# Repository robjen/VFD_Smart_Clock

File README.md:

# VFD_Smart_Clock

A Series of 'socket' designs and firmware running on ESP8266 for IoT smart clock

first draft of working firmware :
https://www.youtube.com/watch?v=jQWC35hEyko

Sockets are 1-4 digits in all sorts of size based on:
* 4 digits IV4/17 16 segment tube
* 1 digit 5x7 IV26 7 point tubes type 1 (fully independant dots) and type 3  (1-2-1-2-1 )
* 2 digits 2x 5x7 IV25 7 point tubes type 1 and type 3 (yes found these on the internet named them as above)
* LED lighting under/behind each tube with a WS2812 RGB 
* HV module on each board so they are fully independant and run from a single 5V supply
* 4 digital lines for easy control passed though each board SPI-clk SPI-data SPI-load BLANK LED-data

Any of the types of socket can be chained, but you might have to mess about with the firmware if you want mix-n-match different types

Firmware provides:
* clock display 
* NTP sync
* auto DST based on timezone
* hidden 'phrases'
* RSS news reader (BBC)
* Ability to add user messages
* Web interface for configuration
* a load of animated transitions and effects
* a few LED effects (more coming soon)

loads of new features coming soon

its a bit of a mess right now but in progress

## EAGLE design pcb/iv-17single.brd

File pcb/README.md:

# eagle cad files for 5 types of PCB

not the best naming convention but load them to see whats what

all of them have been sent off for manufacture at http://dirtypcbs.com and work

simple layout for easy hand soldering including everything in sockets

I switched convention on the IV25 and started calling them type 1 and type 3 to match the IV26 tubes the PCB mask layer reflects that even if the PCB schematic does not

# Tubes ....

well they are getting harder to find but ebay is your friend, also use the 'international' .com site as I find the UK site sometimes hides possible sellers that will still ship to here and quote prices in dollars

# Components 

the main IC ... you can use that maxim part but its pricey or a perfect substitute is the 'HV5812' again ebay is the place to find those

WS2812b again ebay cheap and easy to find in reels ready to solder, that and 1 capacitor are surface mount (on the IV4/17 board) easy enough with a steady hand

the DC-DC module was again an ebay thing (can you spot a trend here!)  there are loads of far east manufactures doing a module that should be about £1 including post per module.  you could use one module to power more than 1 PCB with a fly-lead thats up to you, keeping 1 module per PCB means you can mix and match anything you want. 

# BIG SOLDER TIP

The hardest part can be threading the tubes and getting them all nice and level.

Note the marker point on each PCB, sometimes this is the short (almost removed) pin, sometimes the longest pin, sometimes just a vague guide ... it will depend where you sourced your tubes from, check and check again before you solder as there is no going back. the PCB layout is as per data sheet but these tubes have an element of 'hand made' so not 100% perfect they should face forward give or take a tiny adjustment.

I found that for tubes with few wires it is easy enough to align them all by hand in one go and push whole tube down in one step.

For tubes with lots of wires (IV4/17) start by threading a few on one side then work round with tweezers loading each wire in turn until you can push the whole tube home.

DO NOT use the glass envelope of the tube to try and align the digits, they vary quite a lot internally so allow a gap above the PCB on the first one you solder and alight the 'dots' or digits by eye or with a rule to get them even. If you dont allow a gap on the first one you might find you cant push subsequent ones down low enough ... 

At this point in construction I tended to tape everything down to a spare board as I went so that all the tubes were well aligned and I can fip it up and solder

KEEP YOUR FIRST EXAMPLE at least the first one you are happy with, then you can use it as a guide of height of dot/digit from the PCB for subsequent builds  (I use a scrap early PCB design that had an error but the tubes are neat so its a good guide).

you can adjust tubes a little once soldered but there is a risk you will break the pins or short something if you try and squash the tubes down. you cant really do more than a tiny twist on the IV4/17 tubes

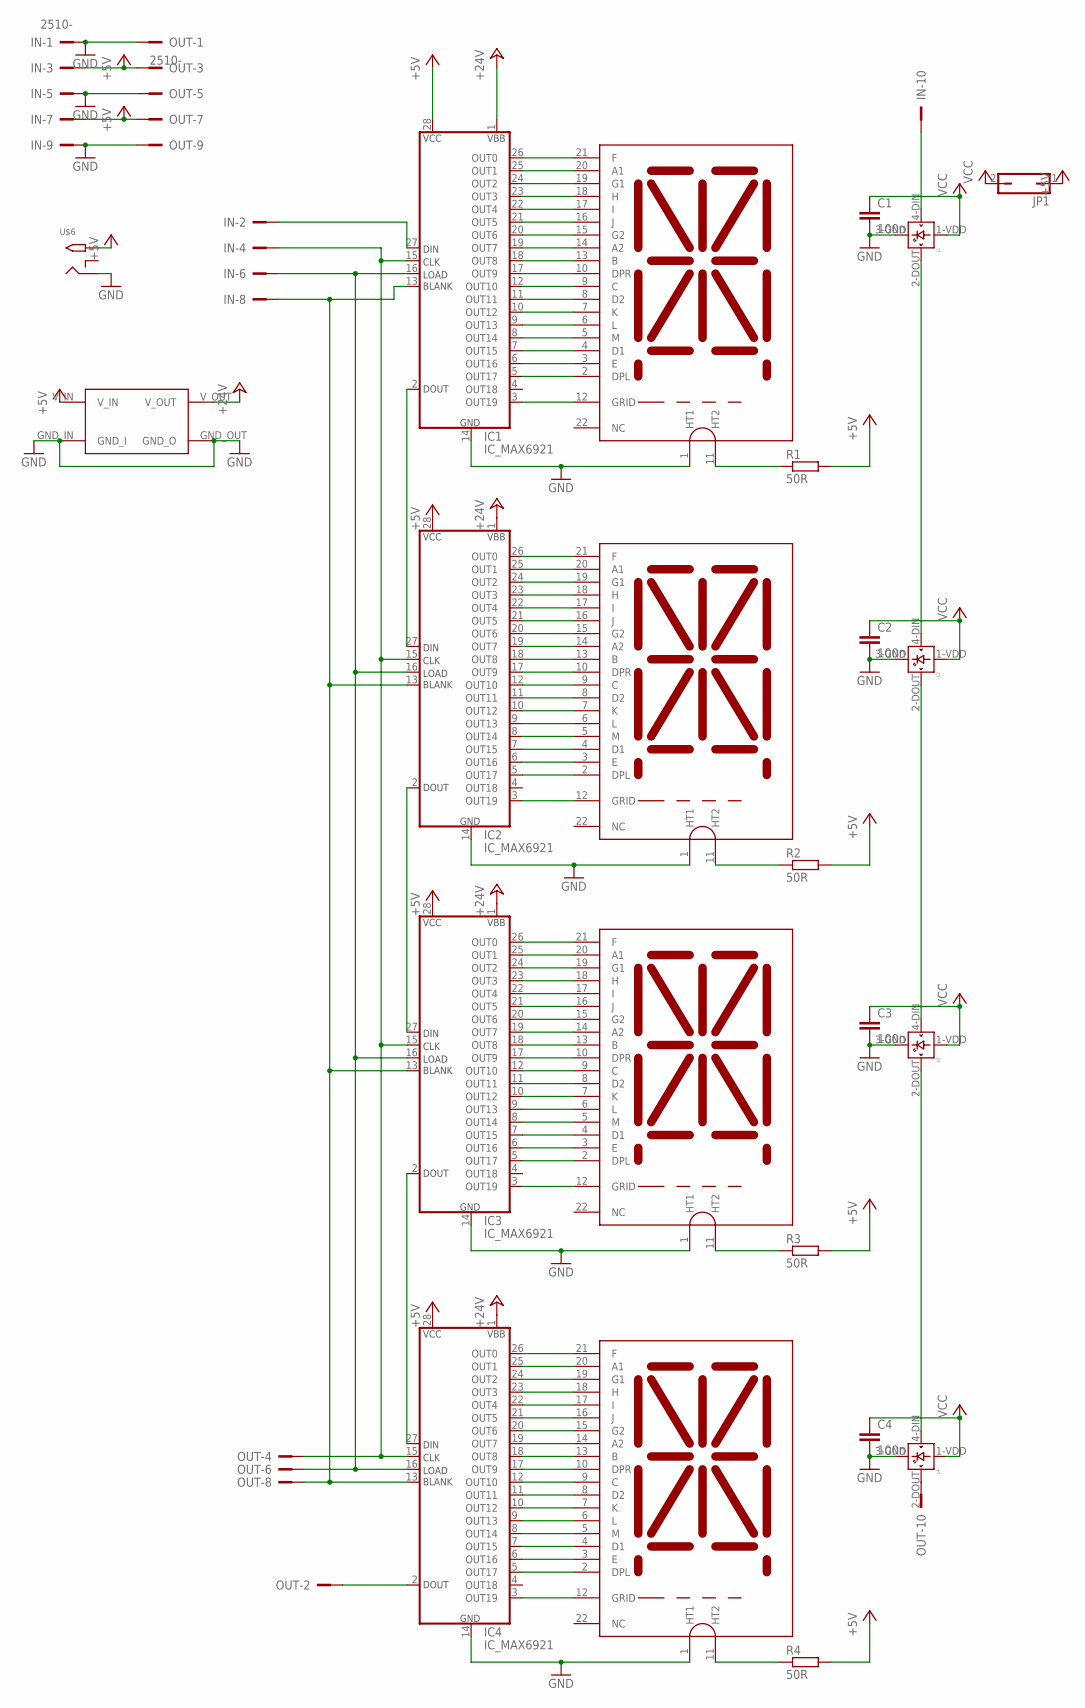
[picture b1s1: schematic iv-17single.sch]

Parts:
1, 2, 3, 4: IV-17_DISPIV-17; IV-17
C1, C2, C3, C4: 100n; C0805
IC1, IC2, IC3, IC4: IC_MAX6921; S28
IN: 2510-; PAK100/2500-10
JP1: JP1Q; JP1
L1, L2, L3, L4: WS2812B
OUT: 2510-; PAK100/2500-10
R1, R2, R3, R4: 50R; 0207/10
U$5: STEP_UP_MODULE
U$6: 2.1MMJACKTHM; PJ-102A

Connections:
+5V: IC1.28 (VCC), IC2.28 (VCC), IC3.28 (VCC), IC4.28 (VCC), IN.3, IN.7, JP1.1, OUT.3, OUT.7, R1.2, R2.2, R3.2, R4.2, U$5.V_IN, U$6.TIP
+24V: IC1.1 (VBB), IC2.1 (VBB), IC3.1 (VBB), IC4.1 (VBB), U$5.V_OUT
GND: 1.1 (HT1), 2.1 (HT1), 3.1 (HT1), 4.1 (HT1), C1.2, C2.2, C3.2, C4.2, IC1.14 (GND), IC2.14 (GND), IC3.14 (GND), IC4.14 (GND), IN.1, IN.5, IN.9, L1.3-GND (GND), L2.3-GND (GND), L3.3-GND (GND), L4.3-GND (GND), OUT.1, OUT.5, OUT.9, U$5.GND_IN (GND_I), U$5.GND_OUT (GND_O), U$6.RING
unnamed: 1.11 (HT2), R1.1
unnamed: 1.21 (F), IC1.26 (OUT0)
unnamed: 1.20 (A1), IC1.25 (OUT1)
unnamed: 1.19 (G1), IC1.24 (OUT2)
unnamed: 1.18 (H), IC1.23 (OUT3)
unnamed: 1.17 (I), IC1.22 (OUT4)
unnamed: 1.16 (J), IC1.21 (OUT5)
unnamed: 1.15 (G2), IC1.20 (OUT6)
unnamed: 1.14 (A2), IC1.19 (OUT7)
unnamed: 1.13 (B), IC1.18 (OUT8)
unnamed: 1.10 (DPR), IC1.17 (OUT9)
unnamed: 1.9 (C), IC1.12 (OUT10)
unnamed: 1.8 (D2), IC1.11 (OUT11)
unnamed: 1.7 (K), IC1.10 (OUT12)
unnamed: 1.6 (L), IC1.9 (OUT13)
unnamed: 1.5 (M), IC1.8 (OUT14)
unnamed: 1.4 (D1), IC1.7 (OUT15)
unnamed: 1.3 (E), IC1.6 (OUT16)
unnamed: 1.2 (DPL), IC1.5 (OUT17)
unnamed: 1.12 (GRID), IC1.3 (OUT19)
unnamed: IC1.27 (DIN), IN.2
unnamed: IC4.2 (DOUT), OUT.2
unnamed: 2.21 (F), IC2.26 (OUT0)
unnamed: L1.2-DOUT (DOUT), L2.4-DIN (DIN)
unnamed: IC1.2 (DOUT), IC2.27 (DIN)
unnamed: 2.20 (A1), IC2.25 (OUT1)
unnamed: 2.19 (G1), IC2.24 (OUT2)
unnamed: 2.18 (H), IC2.23 (OUT3)
unnamed: 2.17 (I), IC2.22 (OUT4)
unnamed: 2.16 (J), IC2.21 (OUT5)
unnamed: 2.15 (G2), IC2.20 (OUT6)
unnamed: 2.14 (A2), IC2.19 (OUT7)
unnamed: 2.13 (B), IC2.18 (OUT8)
unnamed: 2.10 (DPR), IC2.17 (OUT9)
unnamed: 2.9 (C), IC2.12 (OUT10)
unnamed: IC1.15 (CLK), IC2.15 (CLK), IC3.15 (CLK), IC4.15 (CLK), IN.4, OUT.4
unnamed: 2.8 (D2), IC2.11 (OUT11)
unnamed: 2.7 (K), IC2.10 (OUT12)
unnamed: 2.6 (L), IC2.9 (OUT13)
unnamed: 2.5 (M), IC2.8 (OUT14)
unnamed: 2.4 (D1), IC2.7 (OUT15)
unnamed: 2.3 (E), IC2.6 (OUT16)
unnamed: 2.2 (DPL), IC2.5 (OUT17)
unnamed: 2.12 (GRID), IC2.3 (OUT19)
unnamed: IC1.16 (LOAD), IC2.16 (LOAD), IC3.16 (LOAD), IC4.16 (LOAD), IN.6, OUT.6
unnamed: 2.11 (HT2), R2.1
unnamed: 3.21 (F), IC3.26 (OUT0)
unnamed: 3.20 (A1), IC3.25 (OUT1)
unnamed: 3.19 (G1), IC3.24 (OUT2)
unnamed: 3.18 (H), IC3.23 (OUT3)
unnamed: 3.17 (I), IC3.22 (OUT4)
unnamed: 3.16 (J), IC3.21 (OUT5)
unnamed: 3.15 (G2), IC3.20 (OUT6)
unnamed: 3.14 (A2), IC3.19 (OUT7)
unnamed: 3.13 (B), IC3.18 (OUT8)
unnamed: 3.10 (DPR), IC3.17 (OUT9)
unnamed: 3.9 (C), IC3.12 (OUT10)
unnamed: 3.8 (D2), IC3.11 (OUT11)
unnamed: 3.7 (K), IC3.10 (OUT12)
unnamed: 3.6 (L), IC3.9 (OUT13)
unnamed: 3.5 (M), IC3.8 (OUT14)
unnamed: 3.4 (D1), IC3.7 (OUT15)
unnamed: 3.3 (E), IC3.6 (OUT16)
unnamed: 3.2 (DPL), IC3.5 (OUT17)
unnamed: 3.12 (GRID), IC3.3 (OUT19)
unnamed: IC1.13 (BLANK), IC2.13 (BLANK), IC3.13 (BLANK), IC4.13 (BLANK), IN.8, OUT.8
unnamed: 3.11 (HT2), R3.1
unnamed: 4.21 (F), IC4.26 (OUT0)
unnamed: 4.20 (A1), IC4.25 (OUT1)
unnamed: 4.19 (G1), IC4.24 (OUT2)
unnamed: 4.18 (H), IC4.23 (OUT3)
unnamed: 4.17 (I), IC4.22 (OUT4)
unnamed: 4.16 (J), IC4.21 (OUT5)
unnamed: 4.15 (G2), IC4.20 (OUT6)
unnamed: 4.14 (A2), IC4.19 (OUT7)
unnamed: 4.13 (B), IC4.18 (OUT8)
unnamed: 4.10 (DPR), IC4.17 (OUT9)
unnamed: 4.9 (C), IC4.12 (OUT10)
unnamed: 4.8 (D2), IC4.11 (OUT11)
unnamed: 4.7 (K), IC4.10 (OUT12)
unnamed: 4.6 (L), IC4.9 (OUT13)
unnamed: 4.5 (M), IC4.8 (OUT14)
unnamed: 4.4 (D1), IC4.7 (OUT15)
unnamed: 4.3 (E), IC4.6 (OUT16)
unnamed: 4.2 (DPL), IC4.5 (OUT17)
unnamed: 4.12 (GRID), IC4.3 (OUT19)
unnamed: L2.2-DOUT (DOUT), L3.4-DIN (DIN)
unnamed: 4.11 (HT2), R4.1
unnamed: L3.2-DOUT (DOUT), L4.4-DIN (DIN)
unnamed: IN.10, L1.4-DIN (DIN)
unnamed: L4.2-DOUT (DOUT), OUT.10
unnamed: IC2.2 (DOUT), IC3.27 (DIN)
unnamed: IC3.2 (DOUT), IC4.27 (DIN)
VCC: C1.1, C2.1, C3.1, C4.1, JP1.2, L1.1-VDD (VDD), L2.1-VDD (VDD), L3.1-VDD (VDD), L4.1-VDD (VDD)

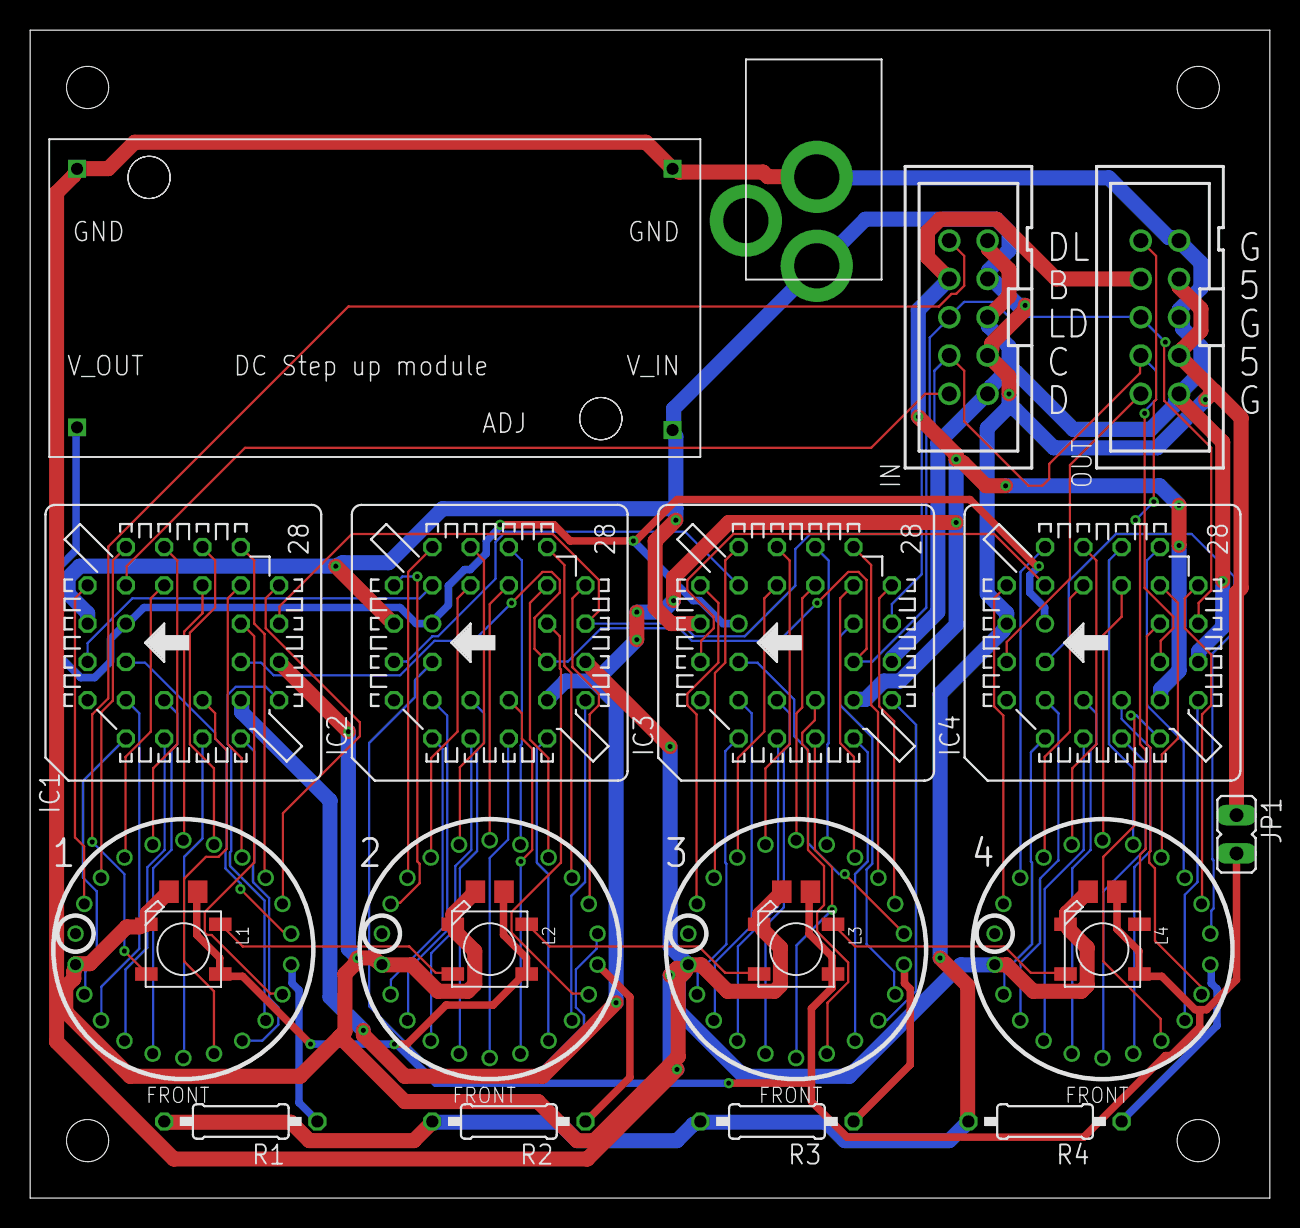
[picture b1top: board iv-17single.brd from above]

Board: 2 copper layers, 82.2 x 77.5 mm, 25 parts (0 on the bottom side), 97 nets.

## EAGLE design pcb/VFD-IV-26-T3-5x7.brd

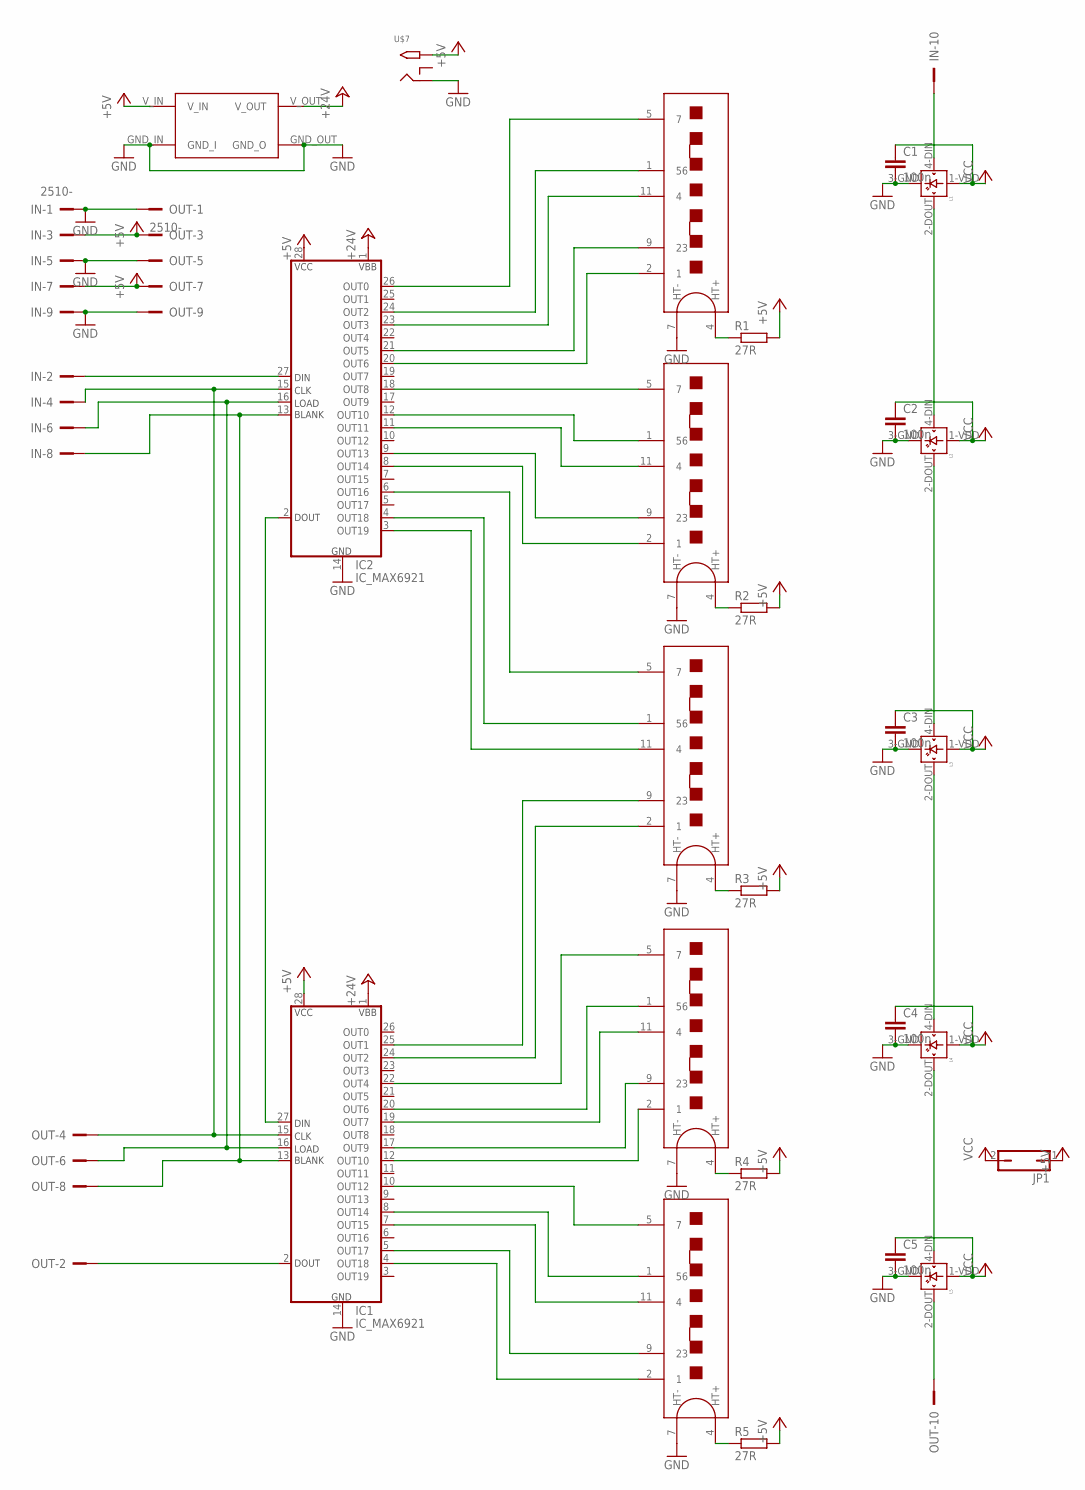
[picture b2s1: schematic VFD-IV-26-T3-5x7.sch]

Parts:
1, 2, 3, 4, 5: IV-26-T3_DISP; IV-26_T2_T3
C1, C2, C3, C4, C5: 100n; C050-025X075
IC1, IC2: IC_MAX6921; S28
IN: 2510-; PAK100/2500-10
JP1: JP1Q; JP1
L1, L2, L3, L4, L5: WS2812B
OUT: 2510-; PAK100/2500-10
R1, R2, R3, R4, R5: 27R; 0207/10
U$6: STEP_UP_MODULE
U$7: 2.1MMJACKTHM; PJ-102A

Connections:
+5V: IC1.28 (VCC), IC2.28 (VCC), IN.3, IN.7, JP1.1, OUT.3, OUT.7, R1.2, R2.2, R3.2, R4.2, R5.2, U$6.V_IN, U$7.TIP
+24V: IC1.1 (VBB), IC2.1 (VBB), U$6.V_OUT
GND: 1.7 (HT-), 2.7 (HT-), 3.7 (HT-), 4.7 (HT-), 5.7 (HT-), C1.2, C2.2, C3.2, C4.2, C5.2, IC1.14 (GND), IC2.14 (GND), IN.1, IN.5, IN.9, L1.3-GND (GND), L2.3-GND (GND), L3.3-GND (GND), L4.3-GND (GND), L5.3-GND (GND), OUT.1, OUT.5, OUT.9, U$6.GND_IN (GND_I), U$6.GND_OUT (GND_O), U$7.RING
unnamed: 1.5 (7), IC2.26 (OUT0)
unnamed: 1.1 (56), IC2.24 (OUT2)
unnamed: 1.11 (4), IC2.23 (OUT3)
unnamed: 1.9 (23), IC2.21 (OUT5)
unnamed: 1.2 (1), IC2.20 (OUT6)
unnamed: 2.5 (7), IC2.18 (OUT8)
unnamed: 2.1 (56), IC2.12 (OUT10)
unnamed: 2.11 (4), IC2.11 (OUT11)
unnamed: 2.9 (23), IC2.9 (OUT13)
unnamed: 2.2 (1), IC2.8 (OUT14)
unnamed: 3.5 (7), IC2.6 (OUT16)
unnamed: 3.1 (56), IC2.4 (OUT18)
unnamed: 3.11 (4), IC2.3 (OUT19)
unnamed: 3.9 (23), IC1.25 (OUT1)
unnamed: 3.2 (1), IC1.24 (OUT2)
unnamed: 4.5 (7), IC1.22 (OUT4)
unnamed: 4.1 (56), IC1.20 (OUT6)
unnamed: 4.11 (4), IC1.19 (OUT7)
unnamed: 4.9 (23), IC1.17 (OUT9)
unnamed: 4.2 (1), IC1.12 (OUT10)
unnamed: 5.5 (7), IC1.10 (OUT12)
unnamed: 5.1 (56), IC1.8 (OUT14)
unnamed: 5.11 (4), IC1.7 (OUT15)
unnamed: 5.9 (23), IC1.5 (OUT17)
unnamed: 5.2 (1), IC1.4 (OUT18)
unnamed: L1.2-DOUT (DOUT), L2.4-DIN (DIN)
unnamed: L2.2-DOUT (DOUT), L3.4-DIN (DIN)
unnamed: L3.2-DOUT (DOUT), L4.4-DIN (DIN)
unnamed: L4.2-DOUT (DOUT), L5.4-DIN (DIN)
unnamed: IC1.15 (CLK), IC2.15 (CLK), IN.4, OUT.4
unnamed: IC1.27 (DIN), IC2.2 (DOUT)
unnamed: IC1.13 (BLANK), IC2.13 (BLANK), IN.8, OUT.8
unnamed: IC1.16 (LOAD), IC2.16 (LOAD), IN.6, OUT.6
unnamed: IC2.27 (DIN), IN.2
unnamed: IN.10, L1.4-DIN (DIN)
unnamed: 2.4 (HT+), R2.1
unnamed: 3.4 (HT+), R3.1
unnamed: 4.4 (HT+), R4.1
unnamed: 5.4 (HT+), R5.1
unnamed: 1.4 (HT+), R1.1
unnamed: IC1.2 (DOUT), OUT.2
unnamed: L5.2-DOUT (DOUT), OUT.10
VCC: C1.1, C2.1, C3.1, C4.1, C5.1, JP1.2, L1.1-VDD (VDD), L2.1-VDD (VDD), L3.1-VDD (VDD), L4.1-VDD (VDD), L5.1-VDD (VDD)

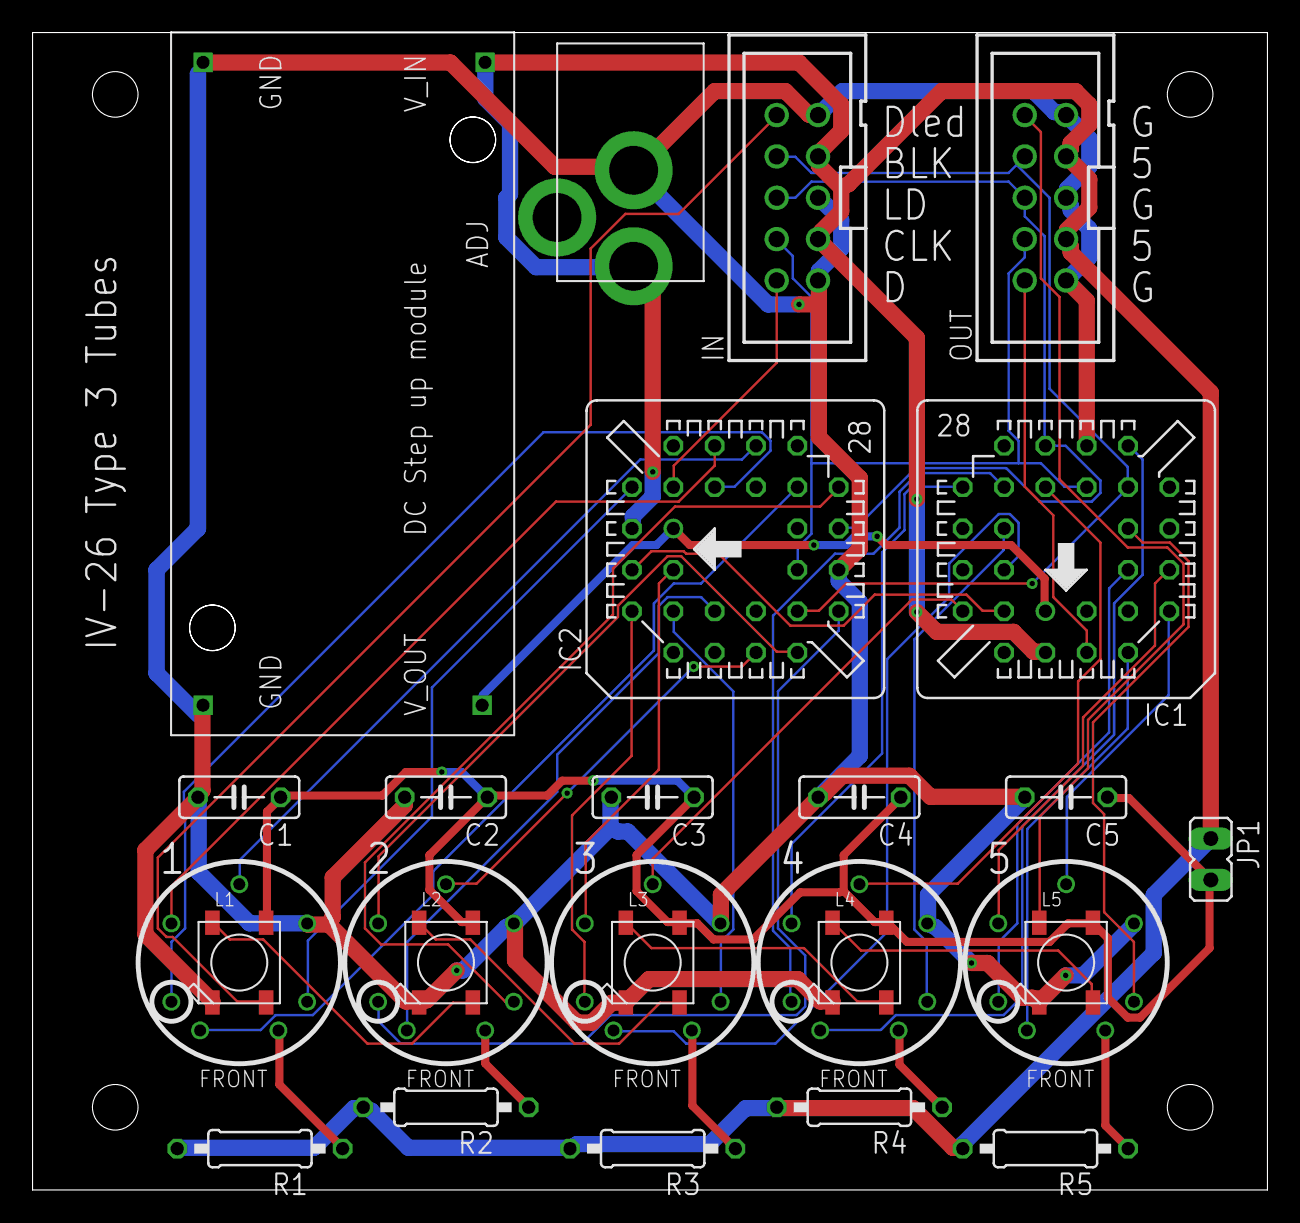
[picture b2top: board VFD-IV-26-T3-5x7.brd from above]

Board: 2 copper layers, 75.9 x 71.1 mm, 27 parts (0 on the bottom side), 46 nets.

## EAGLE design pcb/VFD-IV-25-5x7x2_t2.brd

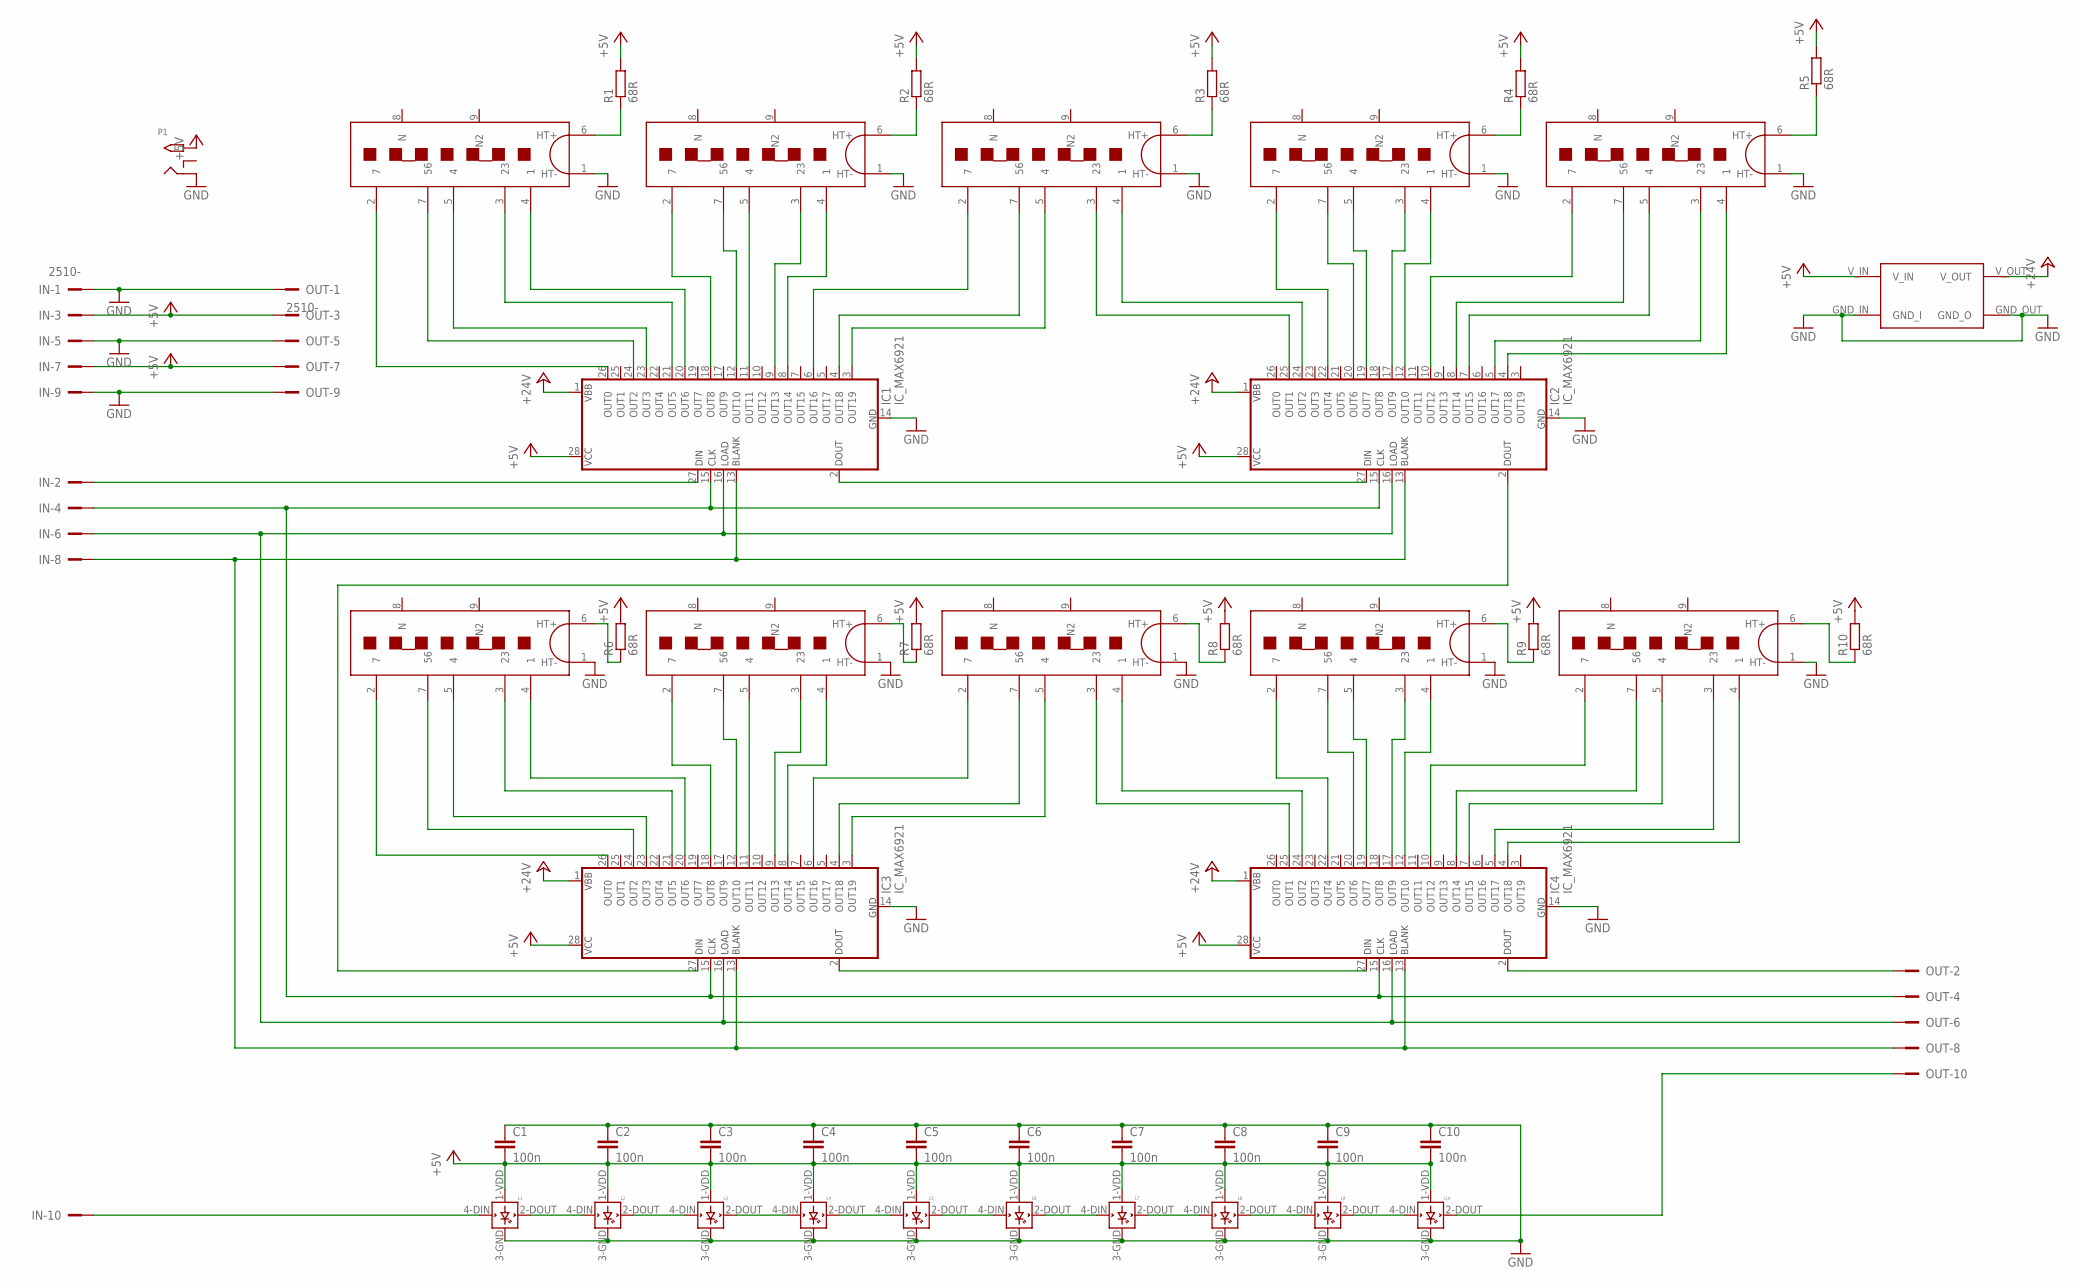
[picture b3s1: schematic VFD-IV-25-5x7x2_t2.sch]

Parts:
1, 2, 3, 4, 5, 6, 7, 8, 9, 10: IV-25_DISP_T3; IV-25
C1, C2, C3, C4, C5, C6, C7, C8, C9, C10: 100n; C050-025X075
IC1, IC2, IC3, IC4: IC_MAX6921; S28
IN: 2510-; PAK100/2500-10
L1, L2, L3, L4, L5, L6, L7, L8, L9, L10: WS2812B
OUT: 2510-; PAK100/2500-10
P1: 2.1MMJACKTHM; PJ-102A
R1, R2, R3, R4, R5, R6, R7, R8, R9, R10: 68R; 0207/10
U$11: STEP_UP_MODULE

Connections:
+5V: C1.2, C2.2, C3.2, C4.2, C5.2, C6.2, C7.2, C8.2, C9.2, C10.2, IC1.28 (VCC), IC2.28 (VCC), IC3.28 (VCC), IC4.28 (VCC), IN.3, IN.7, L1.1-VDD (VDD), L2.1-VDD (VDD), L3.1-VDD (VDD), L4.1-VDD (VDD), L5.1-VDD (VDD), L6.1-VDD (VDD), L7.1-VDD (VDD), L8.1-VDD (VDD), L9.1-VDD (VDD), L10.1-VDD (VDD), OUT.3, OUT.7, P1.TIP, R1.2, R2.2, R3.2, R4.2, R5.2, R6.2, R7.2, R8.2, R9.2, R10.2, U$11.V_IN
+24V: IC1.1 (VBB), IC2.1 (VBB), IC3.1 (VBB), IC4.1 (VBB), U$11.V_OUT
GND: 1.1 (HT-), 2.1 (HT-), 3.1 (HT-), 4.1 (HT-), 5.1 (HT-), 6.1 (HT-), 7.1 (HT-), 8.1 (HT-), 9.1 (HT-), 10.1 (HT-), C1.1, C2.1, C3.1, C4.1, C5.1, C6.1, C7.1, C8.1, C9.1, C10.1, IC1.14 (GND), IC2.14 (GND), IC3.14 (GND), IC4.14 (GND), IN.1, IN.5, IN.9, L1.3-GND (GND), L2.3-GND (GND), L3.3-GND (GND), L4.3-GND (GND), L5.3-GND (GND), L6.3-GND (GND), L7.3-GND (GND), L8.3-GND (GND), L9.3-GND (GND), L10.3-GND (GND), OUT.1, OUT.5, OUT.9, P1.RING, U$11.GND_IN (GND_I), U$11.GND_OUT (GND_O)
unnamed: L1.2-DOUT (DOUT), L2.4-DIN (DIN)
unnamed: L2.2-DOUT (DOUT), L3.4-DIN (DIN)
unnamed: L3.2-DOUT (DOUT), L4.4-DIN (DIN)
unnamed: L4.2-DOUT (DOUT), L5.4-DIN (DIN)
unnamed: L5.2-DOUT (DOUT), L6.4-DIN (DIN)
unnamed: L6.2-DOUT (DOUT), L7.4-DIN (DIN)
unnamed: L7.2-DOUT (DOUT), L8.4-DIN (DIN)
unnamed: L8.2-DOUT (DOUT), L9.4-DIN (DIN)
unnamed: L9.2-DOUT (DOUT), L10.4-DIN (DIN)
unnamed: 1.2 (7), IC1.26 (OUT0)
unnamed: 1.7 (56), IC1.24 (OUT2)
unnamed: 1.5 (4), IC1.23 (OUT3)
unnamed: 1.3 (23), IC1.21 (OUT5)
unnamed: 1.4 (1), IC1.20 (OUT6)
unnamed: 2.2 (7), IC1.18 (OUT8)
unnamed: 2.7 (56), IC1.12 (OUT10)
unnamed: 2.5 (4), IC1.11 (OUT11)
unnamed: 2.3 (23), IC1.9 (OUT13)
unnamed: 2.4 (1), IC1.8 (OUT14)
unnamed: 3.2 (7), IC1.6 (OUT16)
unnamed: 4.2 (7), IC2.22 (OUT4)
unnamed: 3.7 (56), IC1.4 (OUT18)
unnamed: 3.5 (4), IC1.3 (OUT19)
unnamed: 3.3 (23), IC2.25 (OUT1)
unnamed: 3.4 (1), IC2.24 (OUT2)
unnamed: 4.7 (56), IC2.20 (OUT6)
unnamed: 4.5 (4), IC2.19 (OUT7)
unnamed: 4.3 (23), IC2.17 (OUT9)
unnamed: 4.4 (1), IC2.12 (OUT10)
unnamed: 5.2 (7), IC2.10 (OUT12)
unnamed: 5.7 (56), IC2.8 (OUT14)
unnamed: 5.5 (4), IC2.7 (OUT15)
unnamed: 5.3 (23), IC2.5 (OUT17)
unnamed: 5.4 (1), IC2.4 (OUT18)
unnamed: 6.2 (7), IC3.26 (OUT0)
unnamed: 6.7 (56), IC3.24 (OUT2)
unnamed: 6.5 (4), IC3.23 (OUT3)
unnamed: 6.3 (23), IC3.21 (OUT5)
unnamed: 6.4 (1), IC3.20 (OUT6)
unnamed: 7.2 (7), IC3.18 (OUT8)
unnamed: 7.7 (56), IC3.12 (OUT10)
unnamed: 7.5 (4), IC3.11 (OUT11)
unnamed: 7.3 (23), IC3.9 (OUT13)
unnamed: 7.4 (1), IC3.8 (OUT14)
unnamed: 8.2 (7), IC3.6 (OUT16)
unnamed: 8.7 (56), IC3.4 (OUT18)
unnamed: 8.5 (4), IC3.3 (OUT19)
unnamed: 8.3 (23), IC4.25 (OUT1)
unnamed: 8.4 (1), IC4.24 (OUT2)
unnamed: 9.2 (7), IC4.22 (OUT4)
unnamed: 9.7 (56), IC4.20 (OUT6)
unnamed: 9.5 (4), IC4.19 (OUT7)
unnamed: 9.3 (23), IC4.17 (OUT9)
unnamed: 9.4 (1), IC4.12 (OUT10)
unnamed: 10.2 (7), IC4.10 (OUT12)
unnamed: 10.7 (56), IC4.8 (OUT14)
unnamed: 10.5 (4), IC4.7 (OUT15)
unnamed: 10.3 (23), IC4.5 (OUT17)
unnamed: 10.4 (1), IC4.4 (OUT18)
unnamed: IC1.2 (DOUT), IC2.27 (DIN)
unnamed: IC2.2 (DOUT), IC3.27 (DIN)
unnamed: IC3.2 (DOUT), IC4.27 (DIN)
unnamed: IC1.27 (DIN), IN.2
unnamed: IN.10, L1.4-DIN (DIN)
unnamed: L10.2-DOUT (DOUT), OUT.10
unnamed: IC4.2 (DOUT), OUT.2
unnamed: IC1.15 (CLK), IC2.15 (CLK), IC3.15 (CLK), IC4.15 (CLK), IN.4, OUT.4
unnamed: IC1.16 (LOAD), IC2.16 (LOAD), IC3.16 (LOAD), IC4.16 (LOAD), IN.6, OUT.6
unnamed: 5.6 (HT+), R5.1
unnamed: IC1.13 (BLANK), IC2.13 (BLANK), IC3.13 (BLANK), IC4.13 (BLANK), IN.8, OUT.8
unnamed: 4.6 (HT+), R4.1
unnamed: 3.6 (HT+), R3.1
unnamed: 2.6 (HT+), R2.1
unnamed: 1.6 (HT+), R1.1
unnamed: 9.6 (HT+), R9.1
unnamed: 10.6 (HT+), R10.1
unnamed: 8.6 (HT+), R8.1
unnamed: 7.6 (HT+), R7.1
unnamed: 6.6 (HT+), R6.1

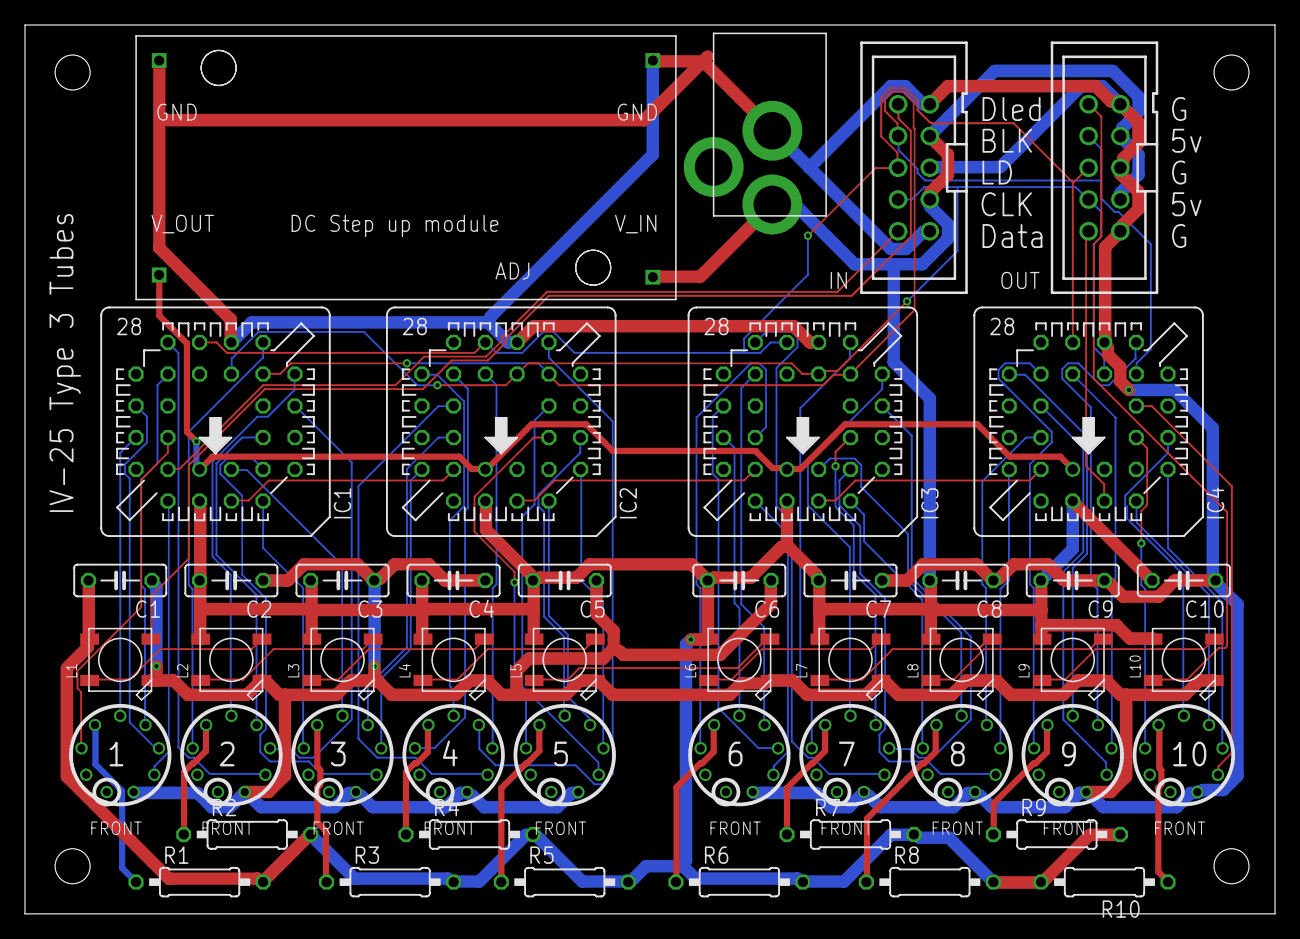
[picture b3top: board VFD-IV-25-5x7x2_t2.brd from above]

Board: 2 copper layers, 100.0 x 71.1 mm, 48 parts (0 on the bottom side), 82 nets.
